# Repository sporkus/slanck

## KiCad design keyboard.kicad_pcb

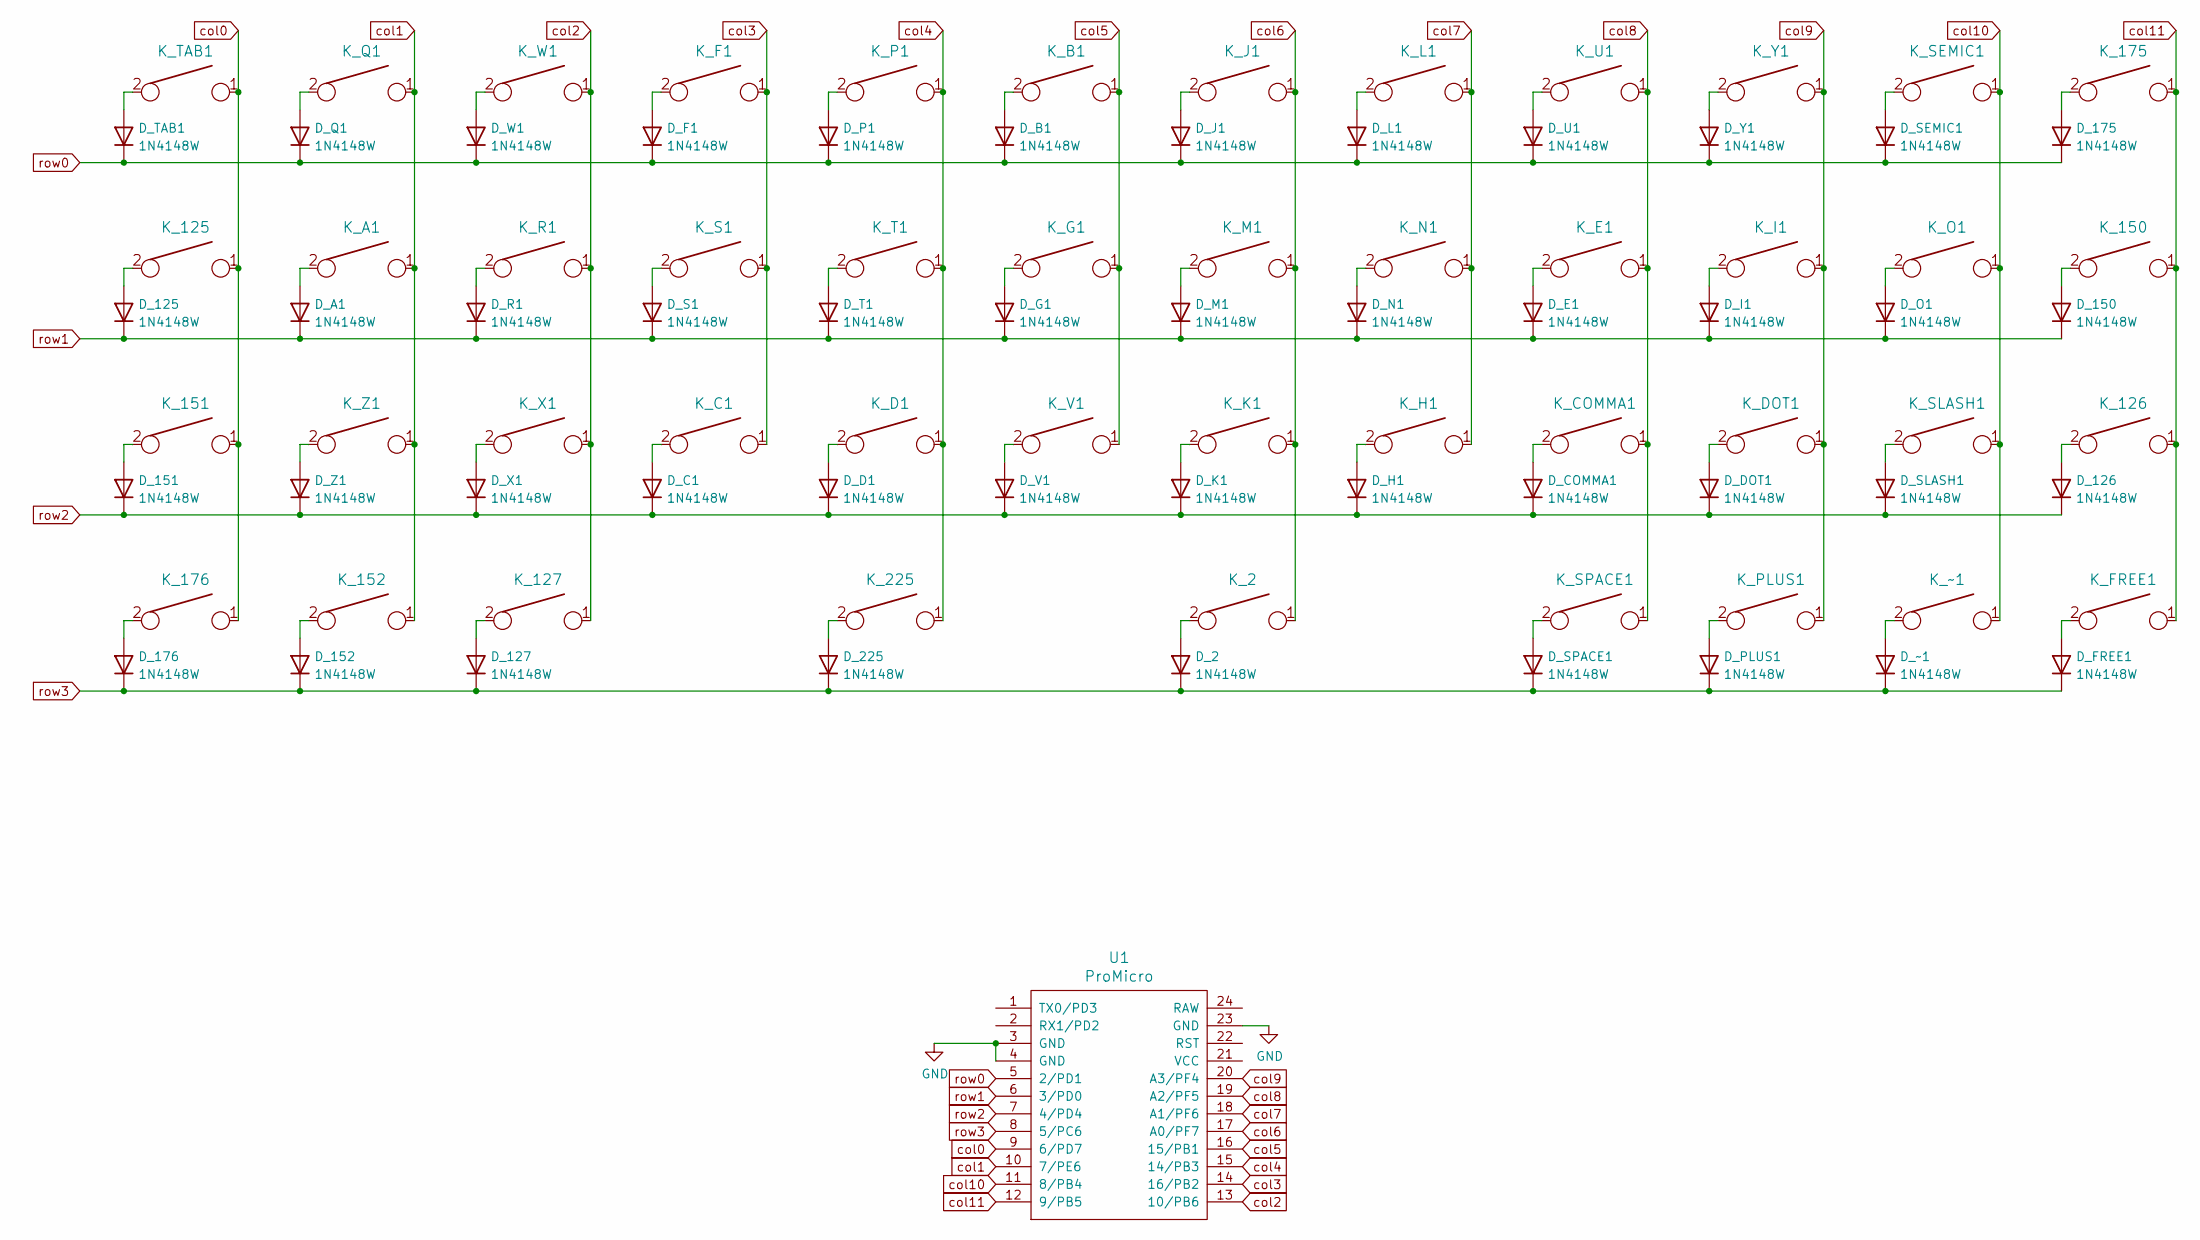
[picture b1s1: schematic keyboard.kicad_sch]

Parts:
D_2, D_125, D_126, D_127, D_150, D_151, D_152, D_175, D_176, D_225: 1N4148W; D_SOD-123; LCSC C81598
D_A1: 1N4148W; D_SOD-123; LCSC C81598
D_B1: 1N4148W; D_SOD-123; LCSC C81598
D_C1: 1N4148W; D_SOD-123; LCSC C81598
D_COMMA1: 1N4148W; D_SOD-123; LCSC C81598
D_D1: 1N4148W; D_SOD-123; LCSC C81598
D_DOT1: 1N4148W; D_SOD-123; LCSC C81598
D_E1: 1N4148W; D_SOD-123; LCSC C81598
D_F1: 1N4148W; D_SOD-123; LCSC C81598
D_FREE1: 1N4148W; D_SOD-123; LCSC C81598
D_G1: 1N4148W; D_SOD-123; LCSC C81598
D_H1: 1N4148W; D_SOD-123; LCSC C81598
D_I1: 1N4148W; D_SOD-123; LCSC C81598
D_J1: 1N4148W; D_SOD-123; LCSC C81598
D_K1: 1N4148W; D_SOD-123; LCSC C81598
D_L1: 1N4148W; D_SOD-123; LCSC C81598
D_M1: 1N4148W; D_SOD-123; LCSC C81598
D_N1: 1N4148W; D_SOD-123; LCSC C81598
D_O1: 1N4148W; D_SOD-123; LCSC C81598
D_P1: 1N4148W; D_SOD-123; LCSC C81598
D_PLUS1: 1N4148W; D_SOD-123; LCSC C81598
D_Q1: 1N4148W; D_SOD-123; LCSC C81598
D_R1: 1N4148W; D_SOD-123; LCSC C81598
D_S1: 1N4148W; D_SOD-123; LCSC C81598
D_SEMIC1: 1N4148W; D_SOD-123; LCSC C81598
D_SLASH1: 1N4148W; D_SOD-123; LCSC C81598
D_SPACE1: 1N4148W; D_SOD-123; LCSC C81598
D_T1: 1N4148W; D_SOD-123; LCSC C81598
D_TAB1: 1N4148W; D_SOD-123; LCSC C81598
D_U1: 1N4148W; D_SOD-123; LCSC C81598
D_V1: 1N4148W; D_SOD-123; LCSC C81598
D_W1: 1N4148W; D_SOD-123; LCSC C81598
D_X1: 1N4148W; D_SOD-123; LCSC C81598
D_Y1: 1N4148W; D_SOD-123; LCSC C81598
D_Z1: 1N4148W; D_SOD-123; LCSC C81598
D_~1: 1N4148W; D_SOD-123; LCSC C81598
K_2: KEYSW; MX-Hotswap-2U
K_125, K_126, K_127: KEYSW; MX-Hotswap-1.25U
K_150, K_151, K_152: KEYSW; MX-Hotswap-1.5U
K_175, K_176: KEYSW; MX-Hotswap-1.75U
K_225: KEYSW; MX-Hotswap-2.25U
K_A1: KEYSW; MX-Hotswap-1U
K_B1: KEYSW; MX-Hotswap-1U
K_C1: KEYSW; MX-Hotswap-1U
K_COMMA1: KEYSW; MX-Hotswap-1U
K_D1: KEYSW; MX-Hotswap-1U
K_DOT1: KEYSW; MX-Hotswap-1U
K_E1: KEYSW; MX-Hotswap-1U
K_F1: KEYSW; MX-Hotswap-1U
K_FREE1: KEYSW; MX-Hotswap-1U
K_G1: KEYSW; MX-Hotswap-1U
K_H1: KEYSW; MX-Hotswap-1U
K_I1: KEYSW; MX-Hotswap-1U
K_J1: KEYSW; MX-Hotswap-1U
K_K1: KEYSW; MX-Hotswap-1U
K_L1: KEYSW; MX-Hotswap-1U
K_M1: KEYSW; MX-Hotswap-1U
K_N1: KEYSW; MX-Hotswap-1U
K_O1: KEYSW; MX-Hotswap-1U
K_P1: KEYSW; MX-Hotswap-1U
K_PLUS1: KEYSW; MX-Hotswap-1U
K_Q1: KEYSW; MX-Hotswap-1U
K_R1: KEYSW; MX-Hotswap-1U
K_S1: KEYSW; MX-Hotswap-1U
K_SEMIC1: KEYSW; MX-Hotswap-1U
K_SLASH1: KEYSW; MX-Hotswap-1U
K_SPACE1: KEYSW; MX-Hotswap-1U
K_T1: KEYSW; MX-Hotswap-1U
K_TAB1: KEYSW; MX-Hotswap-1U
K_U1: KEYSW; MX-Hotswap-1U
K_V1: KEYSW; MX-Hotswap-1U
K_W1: KEYSW; MX-Hotswap-1U
K_X1: KEYSW; MX-Hotswap-1U
K_Y1: KEYSW; MX-Hotswap-1U
K_Z1: KEYSW; MX-Hotswap-1U
K_~1: KEYSW; MX-Hotswap-1U
U1: ProMicro; ArduinoProMicro-ZigZag

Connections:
GND: U1.3 (GND), U1.4 (GND), U1.23 (GND)
unnamed: D_2.2 (A), K_2.2
unnamed: D_125.2 (A), K_125.2
unnamed: D_126.2 (A), K_126.2
unnamed: D_127.2 (A), K_127.2
unnamed: D_150.2 (A), K_150.2
unnamed: D_151.2 (A), K_151.2
unnamed: D_152.2 (A), K_152.2
unnamed: D_175.2 (A), K_175.2
unnamed: D_176.2 (A), K_176.2
unnamed: D_225.2 (A), K_225.2
unnamed: D_A1.2 (A), K_A1.2
unnamed: D_B1.2 (A), K_B1.2
unnamed: D_C1.2 (A), K_C1.2
unnamed: D_COMMA1.2 (A), K_COMMA1.2
unnamed: D_D1.2 (A), K_D1.2
unnamed: D_DOT1.2 (A), K_DOT1.2
unnamed: D_E1.2 (A), K_E1.2
unnamed: D_F1.2 (A), K_F1.2
unnamed: D_FREE1.2 (A), K_FREE1.2
unnamed: D_G1.2 (A), K_G1.2
unnamed: D_H1.2 (A), K_H1.2
unnamed: D_I1.2 (A), K_I1.2
unnamed: D_J1.2 (A), K_J1.2
unnamed: D_K1.2 (A), K_K1.2
unnamed: D_L1.2 (A), K_L1.2
unnamed: D_M1.2 (A), K_M1.2
unnamed: D_N1.2 (A), K_N1.2
unnamed: D_O1.2 (A), K_O1.2
unnamed: D_P1.2 (A), K_P1.2
unnamed: D_PLUS1.2 (A), K_PLUS1.2
unnamed: D_Q1.2 (A), K_Q1.2
unnamed: D_R1.2 (A), K_R1.2
unnamed: D_S1.2 (A), K_S1.2
unnamed: D_SEMIC1.2 (A), K_SEMIC1.2
unnamed: D_SLASH1.2 (A), K_SLASH1.2
unnamed: D_SPACE1.2 (A), K_SPACE1.2
unnamed: D_T1.2 (A), K_T1.2
unnamed: D_TAB1.2 (A), K_TAB1.2
unnamed: D_U1.2 (A), K_U1.2
unnamed: D_V1.2 (A), K_V1.2
unnamed: D_W1.2 (A), K_W1.2
unnamed: D_X1.2 (A), K_X1.2
unnamed: D_Y1.2 (A), K_Y1.2
unnamed: D_Z1.2 (A), K_Z1.2
unnamed: D_~1.2 (A), K_~1.2
col0: K_125.1, K_151.1, K_176.1, K_TAB1.1, U1.9 (6/PD7)
col1: K_152.1, K_A1.1, K_Q1.1, K_Z1.1, U1.10 (7/PE6)
col2: K_127.1, K_R1.1, K_W1.1, K_X1.1, U1.13 (10/PB6)
col3: K_C1.1, K_F1.1, K_S1.1, U1.14 (16/PB2)
col4: K_225.1, K_D1.1, K_P1.1, K_T1.1, U1.15 (14/PB3)
col5: K_B1.1, K_G1.1, K_V1.1, U1.16 (15/PB1)
col6: K_2.1, K_J1.1, K_K1.1, K_M1.1, U1.17 (A0/PF7)
col7: K_H1.1, K_L1.1, K_N1.1, U1.18 (A1/PF6)
col8: K_COMMA1.1, K_E1.1, K_SPACE1.1, K_U1.1, U1.19 (A2/PF5)
col9: K_DOT1.1, K_I1.1, K_PLUS1.1, K_Y1.1, U1.20 (A3/PF4)
col10: K_O1.1, K_SEMIC1.1, K_SLASH1.1, K_~1.1, U1.11 (8/PB4)
col11: K_126.1, K_150.1, K_175.1, K_FREE1.1, U1.12 (9/PB5)
row0: D_175.1 (K), D_B1.1 (K), D_F1.1 (K), D_J1.1 (K), D_L1.1 (K), D_P1.1 (K), D_Q1.1 (K), D_SEMIC1.1 (K), D_TAB1.1 (K), D_U1.1 (K), D_W1.1 (K), D_Y1.1 (K), U1.5 (2/PD1)
row1: D_125.1 (K), D_150.1 (K), D_A1.1 (K), D_E1.1 (K), D_G1.1 (K), D_I1.1 (K), D_M1.1 (K), D_N1.1 (K), D_O1.1 (K), D_R1.1 (K), D_S1.1 (K), D_T1.1 (K), U1.6 (3/PD0)
row2: D_126.1 (K), D_151.1 (K), D_C1.1 (K), D_COMMA1.1 (K), D_D1.1 (K), D_DOT1.1 (K), D_H1.1 (K), D_K1.1 (K), D_SLASH1.1 (K), D_V1.1 (K), D_X1.1 (K), D_Z1.1 (K), U1.7 (4/PD4)
row3: D_2.1 (K), D_127.1 (K), D_152.1 (K), D_176.1 (K), D_225.1 (K), D_FREE1.1 (K), D_PLUS1.1 (K), D_SPACE1.1 (K), D_~1.1 (K), U1.8 (5/PC6)

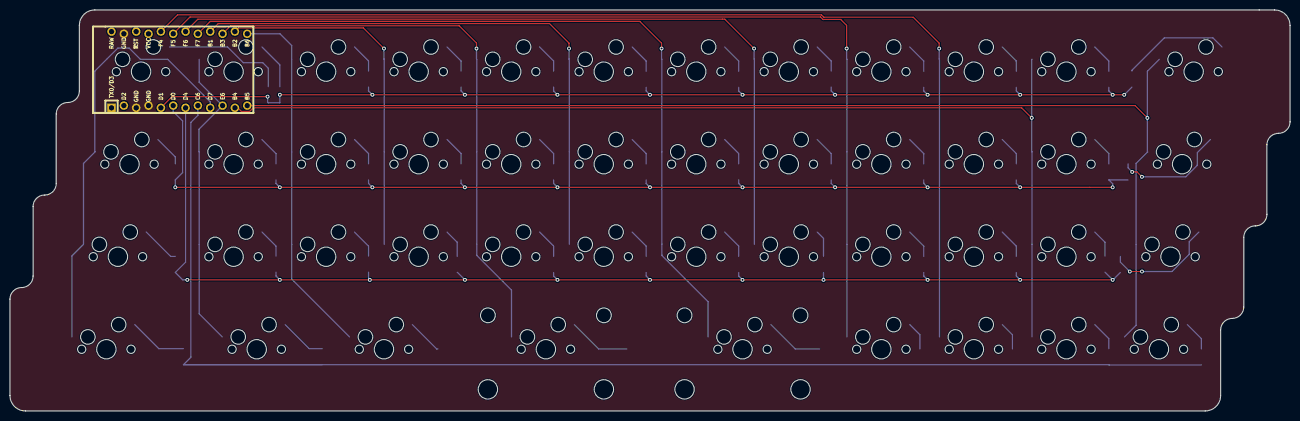
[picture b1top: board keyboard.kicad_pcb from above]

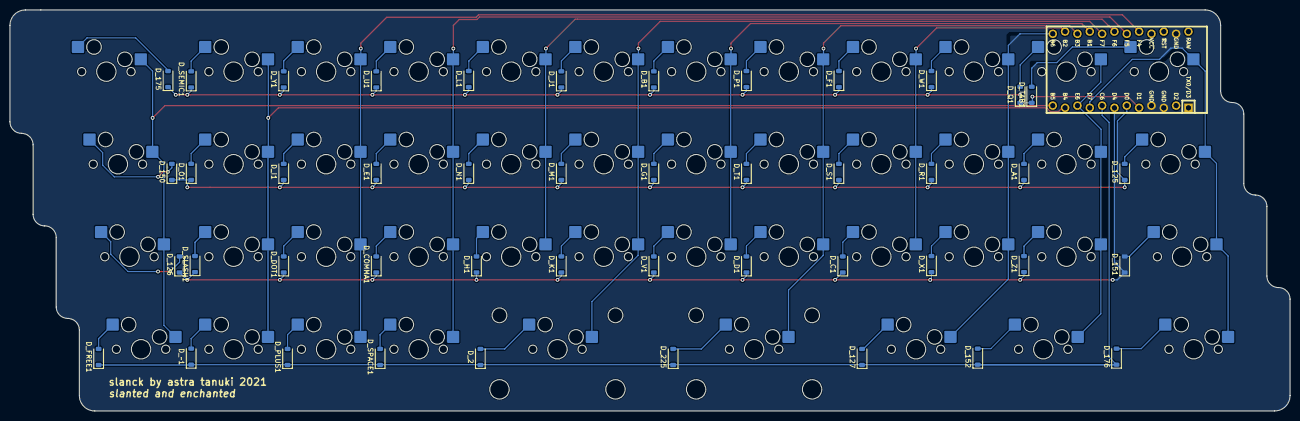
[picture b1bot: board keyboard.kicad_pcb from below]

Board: 2 copper layers, 263.5 x 82.5 mm, 91 parts (45 on the bottom side), 62 nets.

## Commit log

2023-06-06 hotswap ver
2023-06-06 updated bom
2023-06-06 clean up
